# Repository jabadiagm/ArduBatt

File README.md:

# ArduBatt
Cargador de baterías con arduino y pantalla táctil

Cargador de baterías basado en un convertidor push-pull de 30W, controlado por un atmega328p, el mismo que utiliza el arduino Uno. Esto permite usar las herramientas y librerías de arduino. El ajuste del cargador se hace desde una pantalla táctil Nextion, que se comunica con el atmega a través del puerto serie.

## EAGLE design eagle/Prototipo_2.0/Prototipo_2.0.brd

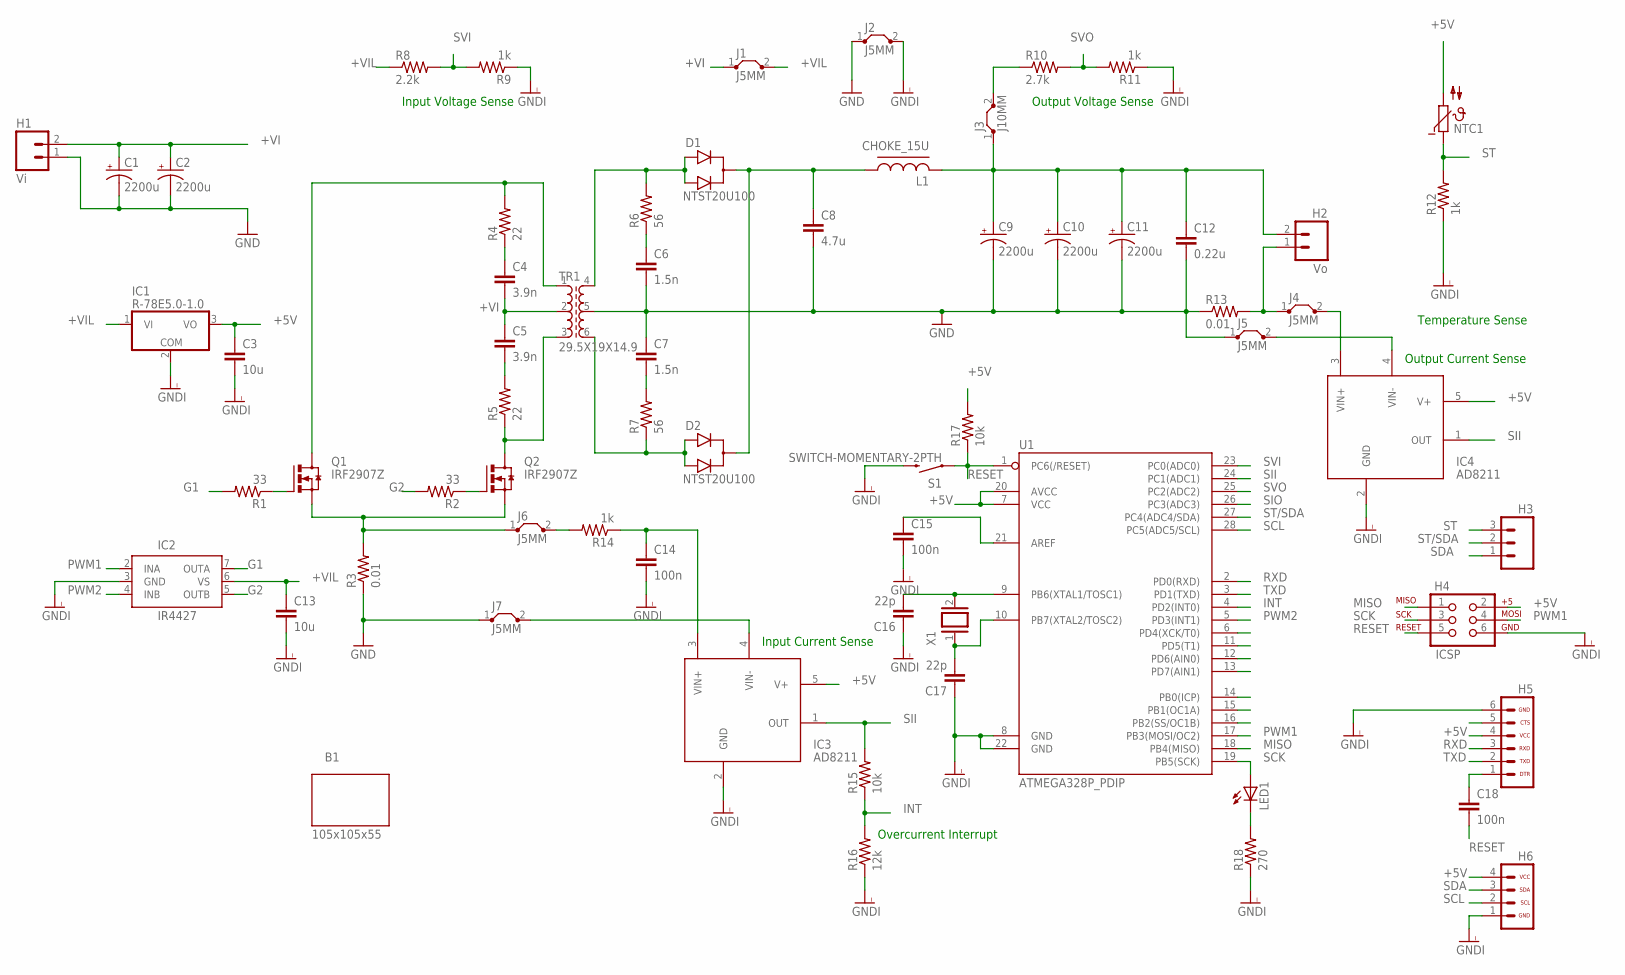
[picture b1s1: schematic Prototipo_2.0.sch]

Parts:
B1: 105x105x55; BOX_105X105X55
C1, C2, C9, C10, C11: 2200u; CPOL_RADIAL_12.5MM_5MM; MOUSER 667-EEU-FR1V222L
C3, C13: 10u; C5B2.5; MOUSER 810-FK26X7R1C106K
C4, C5: 3.9n; C7.5B3; MOUSER 594-K392K15X7RF53L2
C6, C7: 1.5n; C7.5B3; MOUSER 581-SR151C152KAR
C8: 4.7u; C5B2.5; MOUSER 81-RDEC71H475K2M1H3A
C12: 0.22u; C5B3; MOUSER 80-R82DC3220AA60K
C14, C15, C18: 100n; C5B3; MOUSER 80-R82DC3100AA50J
C16, C17: 22p; C5B2.5; MOUSER 140-50N5-220J-RC
D1, D2: NTST20U100; TO220V
H1: Vi; SCREWTERMINAL-5MM-2
H2: Vo; SCREWTERMINAL-5MM-2
H3: M03PTH; 1X03
H4: ICSP; 2X3
H5: HEADER_SERIAL
H6: HEADER_I2C
IC1: R-78E5.0-1.0
IC2: IR4427; DIL08
IC3, IC4: AD8211; RJ-5
J1, J2, J4, J5, J6, J7: J5MM; 05
J3: J10MM; 10
L1: CHOKE_15U; MOUSER 652-2200LL-150-H-RC
LED1: LED5MM
NTC1: NTC640; P640; MOUSER 594-NTCLE203E3502JB0
Q1, Q2: IRF2907Z; TO220V
R1, R2: 33; AXIAL-0.4; MOUSER 660-MF14DCT52R33R0F
R3, R13: 0.01; RSENSE; MOUSER 5W_66-OAR5R010JLF
R4, R5: 22; AXIAL-0.5; MOUSER 603-MFR50SFTE52-22R
R6, R7: 56; AXIAL-0.5; MOUSER 603-MFR50SFTE52-56R
R8: 2.2k; AXIAL-0.4; MOUSER 660-MF1/4DC1001F
R9, R11, R12, R14: 1k; AXIAL-0.4; MOUSER 660-MF1/4DC1001F
R10: 2.7k; AXIAL-0.4
R15, R17: 10k; AXIAL-0.4; MOUSER 660-MF1/4DC1002F
R16: 12k; AXIAL-0.4; MOUSER 660-MF1/4DCT52R1202F
R18: 270; AXIAL-0.4; MOUSER 660-MF1/4DC2700F
S1: SWITCH-MOMENTARY-2PTH; TACTILE-PTH
TR1: 29.5X19X14.9; CORE_29.5X19X14.9
U1: ATMEGA328P_PDIP; DIL28-3; MOUSER 556-ATMEGA328P-PU
X1: XTAL/S; QS

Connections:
$N1: C8.1, D1.2 (C), D2.2 (C), L1.1
+5V: C3.1, H4.2, H5.4 (4_VCC), H6.4 (4_VCC), IC1.3 (VO), IC3.5 (V+), IC4.5 (V+), NTC1.2, R17.P$2 (2), U1.7 (VCC), U1.20 (AVCC)
+VI: C1.+, C2.+, C4.2, C5.1, H1.2, J1.1, TR1.2
+VIL: C13.1, IC1.1 (VI), IC2.6 (VS), J1.2, R8.P$1 (1)
G1: IC2.7 (OUTA), R1.P$2 (2)
G2: IC2.5 (OUTB), R2.P$2 (2)
GND: C1.-, C2.-, C6.2, C7.1, C8.2, C9.-, C10.-, C11.-, C12.2, H1.1, J2.1, J5.1, J7.1, R3.P$1 (1), R13.P$1 (1), TR1.5
GNDI: C3.2, C13.2, C14.2, C15.2, C16.1, C17.1, H4.6, H5.6 (6_GND), H6.1 (1_GND), IC1.2 (COM), IC2.3 (GND), IC3.2 (GND), IC4.2 (GND), J2.2, R9.P$1 (1), R11.P$1 (1), R12.P$1 (1), R16.P$1 (1), R18.P$1 (1), S1.3 (2), U1.8 (GND), U1.22 (GND)
INT: R15.P$1 (1), R16.P$2 (2), U1.4 (PD2(INT0))
MISO: H4.1, U1.18 (PB4(MISO))
unnamed: Q1.1 (G), R1.P$1 (1)
unnamed: Q2.1 (G), R2.P$1 (1)
unnamed: C18.1, H5.1 (1_DTR)
unnamed: C7.2, R7.P$2 (2)
unnamed: C5.2, R5.P$2 (2)
unnamed: J3.2, R10.P$1 (1)
unnamed: C6.1, R6.P$1 (1)
unnamed: D1.1 (A1), D1.3 (A2), R6.P$2 (2), TR1.4
unnamed: D2.1 (A1), D2.3 (A2), R7.P$1 (1), TR1.6
unnamed: C9.+, C10.+, C11.+, C12.1, H2.2, J3.1, L1.2
unnamed: C4.1, R4.P$1 (1)
unnamed: Q1.2 (D), R4.P$2 (2), TR1.1
unnamed: Q2.2 (D), R5.P$1 (1), TR1.3
unnamed: J6.1, Q1.3 (S), Q2.3 (S), R3.P$2 (2)
unnamed: H2.1, J4.1, R13.P$2 (2)
unnamed: IC4.3 (VIN+), J4.2
unnamed: IC4.4 (VIN-), J5.2
unnamed: C14.1, IC3.3 (VIN+), R14.P$1 (1)
unnamed: IC3.4 (VIN-), J7.2
unnamed: J6.2, R14.P$2 (2)
unnamed: C16.2, U1.9 (PB6(XTAL1/TOSC1)), X1.2
unnamed: C17.2, U1.10 (PB7(XTAL2/TOSC2)), X1.1
unnamed: LED1.K (C), R18.P$2 (2)
unnamed: C15.1, U1.21 (AREF)
PWM1: H4.4, IC2.2 (INA), U1.17 (PB3(MOSI/OC2))
PWM2: IC2.4 (INB), U1.5 (PD3(INT1))
RESET: C18.2, H4.5, R17.P$1 (1), S1.1, U1.1 (PC6(/RESET))
RXD: H5.3 (3_RXD), U1.2 (PD0(RXD))
SCK: H4.3, LED1.A, U1.19 (PB5(SCK))
SCL: H6.2 (2_SCL), U1.28 (PC5(ADC5/SCL))
SDA: H3.1, H6.3 (3_SDA)
SII: IC3.1 (OUT), IC4.1 (OUT), R15.P$2 (2), U1.24 (PC1(ADC1))
SIO: U1.26 (PC3(ADC3))
ST: H3.3, NTC1.1, R12.P$2 (2)
ST/SDA: H3.2, U1.27 (PC4(ADC4/SDA))
SVI: R8.P$2 (2), R9.P$2 (2), U1.23 (PC0(ADC0))
SVO: R10.P$2 (2), R11.P$2 (2), U1.25 (PC2(ADC2))
TXD: H5.2 (2_TXD), U1.3 (PD1(TXD))

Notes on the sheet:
Temperature Sense
Input Voltage Sense
Output Voltage Sense
Output Current Sense
Input Current Sense
Overcurrent Interrupt

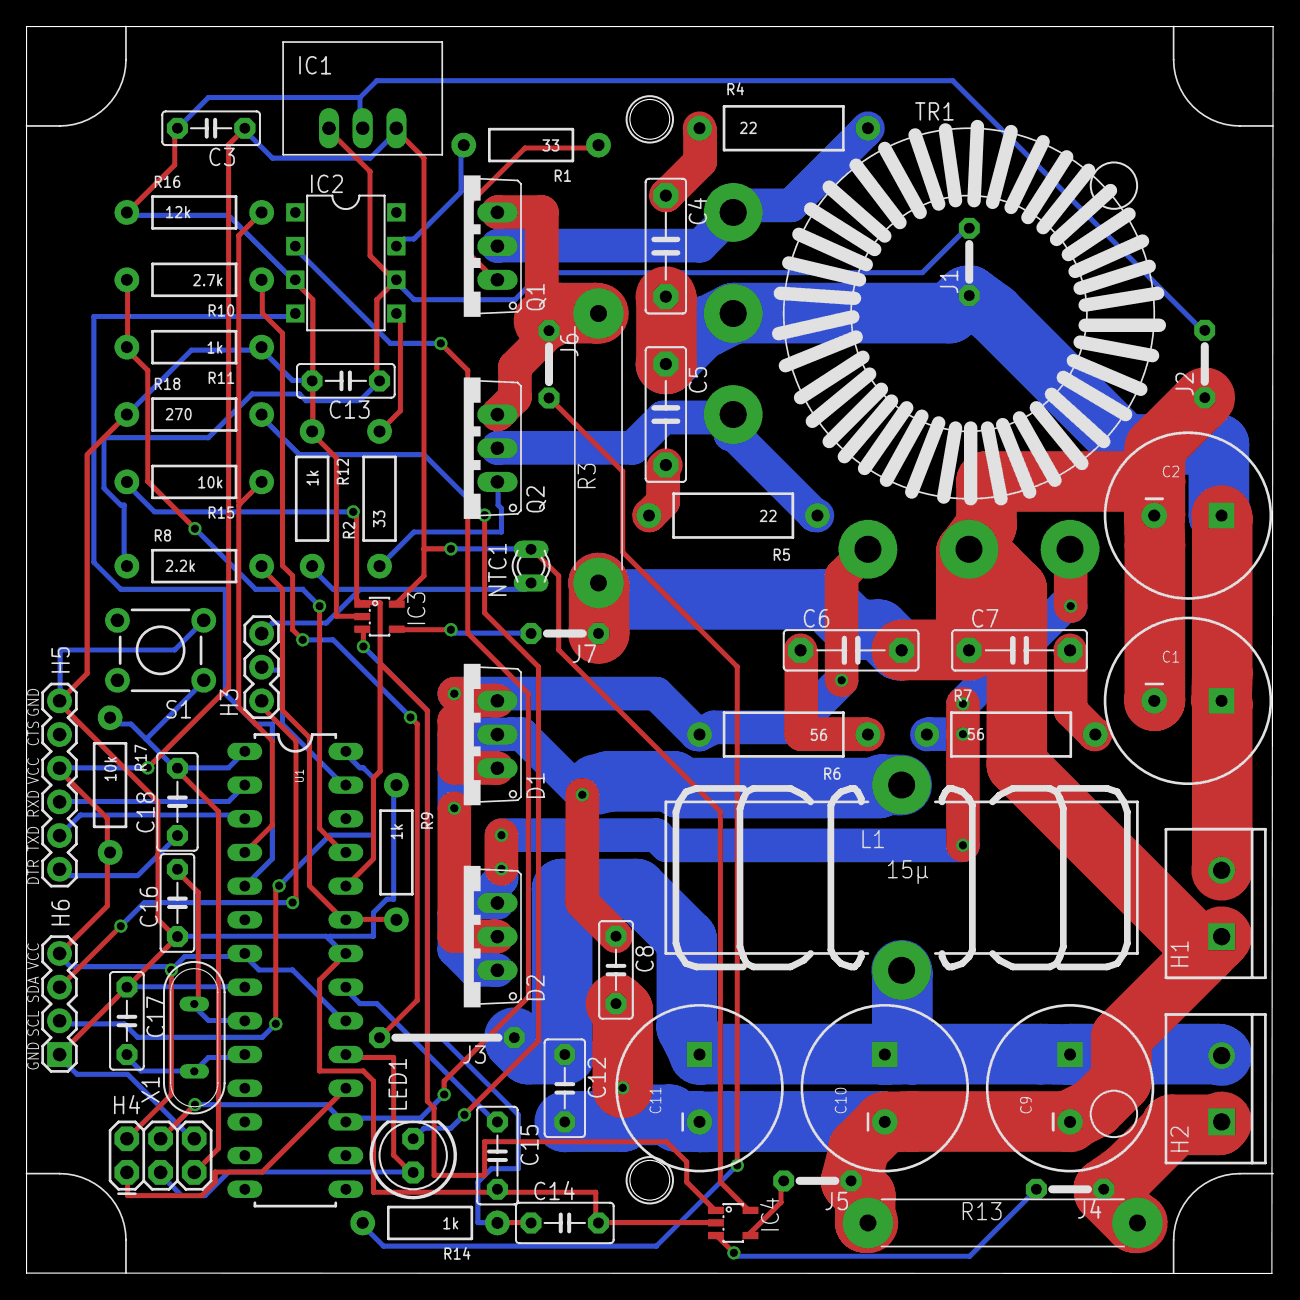
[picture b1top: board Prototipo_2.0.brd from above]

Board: 2 copper layers, 94.0 x 94.0 mm, 65 parts (0 on the bottom side), 47 nets.

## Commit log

2020-06-15 primera versión
2020-06-15 correcciones

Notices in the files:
parts and their libraries:
SparkFun-Passives: Licensing: CC v3.0 Share-Alike You are welcome to use this library for commercial purposes.
SparkFun-DigitalIC: Licensing: Creative Commons ShareAlike 4.0 International - https://creativecommons.org/licenses/by-sa/4.0
